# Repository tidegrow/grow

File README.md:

# Tidegrow Grow

Tidegrow Grow is an experimental low-power grow light system. Boards can be chained to create custom panels.

This repo contains schematics, PCB layouts, firmware and 3D-printable components.

Find more information on the [Grow product page](https://machdyne.com/product/tidegrow-grow/).

## Pinouts

### Zwölf

Grow has a [Zwölf](https://github.com/machdyne/zwolf) MCU socket that can be used to implement a timer, PWM dimming, I2C remote control, etc.

| Pin | Signal | Description |
| --- | ------ | ----------- |
| 1 | SCL | I2C clock |
| 2 | SDA | I2C data |
| 3 | EN | Float = ON, Low = OFF |
| 4 | TEMP | Board temperature (0V - 1.1V) |
| 5 | GND | Ground |
| 6 | 3V3 | Power (3.3V) |

### I2C Headers

Grow has two I2C headers for optional remote control and I2C chaining.

```
SCL SDA GND GND
```

## Notes

These are being tested in 0.6W and 1.2W configurations. The higher power can be acheived by changing R6 from a 2ohm to 1ohm resistor.

The footprints support either four LM301B or four 2835 LEDs.

## LLM-generated code

To the extent that there is LLM-generated code in this repo, it should be space indented. Any space indented code should be carefully audited and then converted to tabs (eventually). 

## License

The contents of this repo are released under the [Lone Dynamics Open License](LICENSE.md).

Note: You can use these designs for commercial purposes but we ask that instead of producing exact clones, that you either replace our trademarks and logos with your own or add your own next to ours.

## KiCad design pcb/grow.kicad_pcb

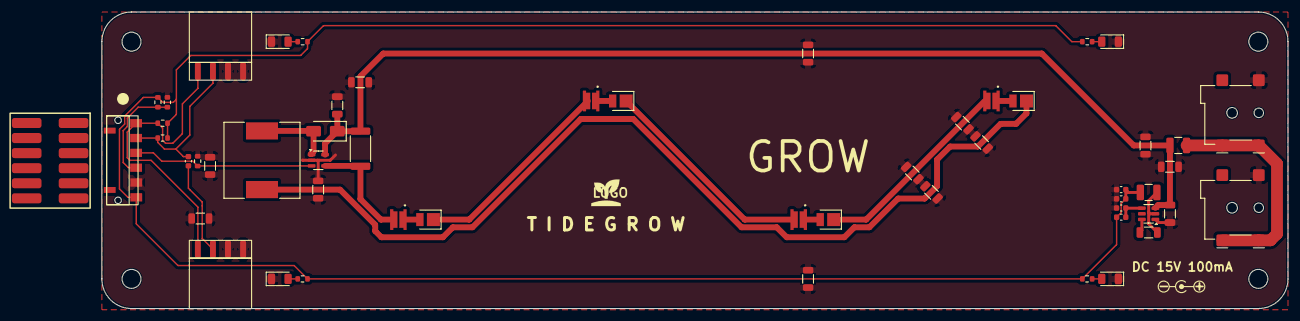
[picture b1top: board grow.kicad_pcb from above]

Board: 2 copper layers, 200.0 x 50.0 mm, 58 parts (0 on the bottom side), 25 nets.

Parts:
C4, C6: 10uF30v; C_1206_3216Metric
C8: 100nF30v; C_1206_3216Metric
C9, C10: 22uF; C_0603_1608Metric
D1: SS34; D_SMA
D2, D3, D4, D5: LM301B; LED_SPMWHD32AMD5XAU0S0
D6, D7, D8, D20: LED; LED_1206_3216Metric
D9, D10, D11, D12: 660nm; LED_PLCC_2835_KBIG
F2: 1A_TRIP; Fuse_1210_3225Metric
H1, H2, H3, H4: MountingHole; MountingHole_3.2mm_M3_DIN965
J1, J5: Conn_01x04_Socket; LD-SMD-FEMALE-1x04
J2, J3: Barrel_Jack_Switch; BarrelJack_Wuerth_694108106102_2.5x5.5mm
J4: Conn_01x06; SPRING-MALE-6P-TIGHTHOLES
L1: 47uH_1.2A_CMLH1204S470MTT; L_SXN_SMDRI127
L4: 3.3uH 1.2A; L_1210_3225Metric
R1, R2, R18: 10K; R_0603_1608Metric
R3, R4, R5, R7: 1K; R_0603_1608Metric
R6: 2000mOhm; R_2512_6332Metric
R8, R11, R12, R13, R14, R15, R15#2, R17, R19, R20, R24, R25: 0R; R_1206_3216Metric
R9: 33K2; C_0603_1608Metric
R10: 10K; C_0603_1608Metric
R16: 0R; C_0603_1608Metric
R21: 20K; R_0603_1608Metric
TH1: Thermistor_NTC; R_0603_1608Metric
U2: PAM2861; SOT-23-5
U3: LD-ZWOLF
U4: AP62300TWU-7; TSOT-23-6

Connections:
/LN: D12.1_1, L1.1
/PWM_LEDW: J4.3, R18.2, U2.3 (VSET)
/PWR3V3: C9.1, C10.1, J4.6, L4.2, R1.2, R2.2, R3.2, R4.2, R5.2, R7.2, R9.2, R21.2
/PWRFUSED: C4.1, C6.1, D1.1 (K), F2.2, R6.1, U2.5 (VIN), U4.3 (VIN)
/PWRIN: F2.1, J2.1, J3.1
/SCL: J1.4, J4.1, J5.1, R2.1
/SDA: J1.3, J4.2, J5.2, R1.1, R16.1, R16.2
/SW: C8.2, L4.1, U4.2 (SW)
/TEMP: J4.4, R21.1, TH1.1
GND: C4.2, C6.2, C9.2, C10.2, D6.1 (K), D7.1 (K), D8.1 (K), D20.1 (K), J1.1, J1.2, J2.2, J3.2, J4.5, J5.3, J5.4, R8.1, R8.2, R10.1, R11.1, R11.2, R12.1, R12.2, R13.1, R13.2, R14.1, R14.2, R15.1, R15.2, R15#2.1, R15#2.2, R17.1, R17.2, R18.1, R19.1, R19.2, R20.1, R20.2, R24.1, R24.2, R25.1, R25.2, TH1.2, U2.2 (GND), U4.1 (GND)
unnamed: D1.2 (A), L1.2, U2.1 (LX)
unnamed: D2.1_1, D2.1_2, D9.2_2
unnamed: D3.2_1, D3.2_2, D9.1_1
unnamed: D6.2 (A), R4.1
unnamed: D7.2 (A), R5.1
unnamed: D8.2 (A), R7.1
unnamed: D4.2_1, D4.2_2, D10.1_1
unnamed: D3.1_1, D3.1_2, D10.2_2
unnamed: D5.2_1, D5.2_2, D11.1_1
unnamed: D4.1_1, D4.1_2, D11.2_2
unnamed: D5.1_1, D5.1_2, D12.2_2
unnamed: D20.2 (A), R3.1
unnamed: D2.2_1, D2.2_2, R6.2, U2.4 (ISENSE)
unnamed: C8.1, U4.6 (BST)
unnamed: R9.1, R10.2, U4.4 (FB)

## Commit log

2026-01-30 add render
